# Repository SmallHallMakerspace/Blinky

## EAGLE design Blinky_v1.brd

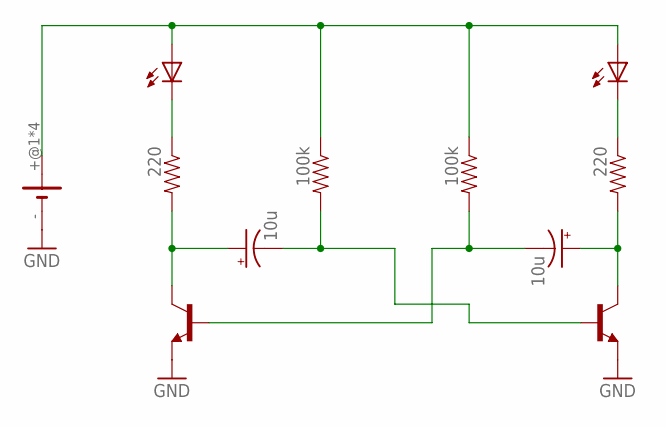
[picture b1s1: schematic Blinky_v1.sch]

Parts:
BT1: BAT-HLD-001-THM; LINX_BAT-HLD-001-THM
C1, C2: 10u; CPOL-RADIAL-10UF-25V
LED1, LED2: RED; LED5MM
R1, R2: 220; AXIAL-0.3
R3, R4: 100k; AXIAL-0.3
U$1, U$2: TRANSISTOR_NPN_2PTH; TO-92

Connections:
GND: BT1.-, U$1.3 (E), U$2.3 (E)
unnamed: LED2.K (C), R2.P$1 (1)
unnamed: C2.1 (+), R2.P$2 (2), U$2.1 (C)
unnamed: LED1.K (C), R1.P$1 (1)
unnamed: C1.1 (+), R1.P$2 (2), U$1.1 (C)
unnamed: BT1.+@1 (+), BT1.+@2 (+), BT1.+@3 (+), BT1.+@4 (+), LED1.A, LED2.A, R3.P$1 (1), R4.P$1 (1)
unnamed: C1.2 (-), R3.P$2 (2), U$2.2 (B)
unnamed: C2.2 (-), R4.P$2 (2), U$1.2 (B)

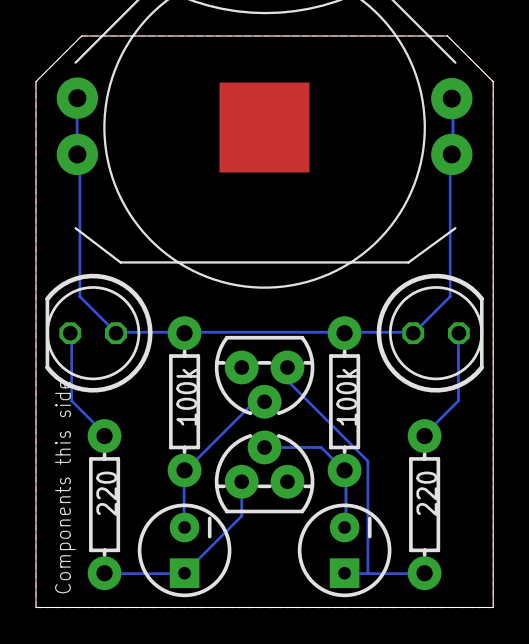
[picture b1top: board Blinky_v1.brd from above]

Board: 2 copper layers, 25.4 x 31.8 mm, 11 parts (0 on the bottom side), 8 nets.

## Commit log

2016-08-12 Initial import, very similar to what was ordered from OSH Park on August 11, 2016.
2016-08-12 Ignore files that eagle creates.
2016-08-12 Added good and bad soldering image, top and bottom text. All on bottom silkscreen.

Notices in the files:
Blinky_v1.brd:
Licensed CC-BY-SA
parts and their libraries:
SparkFun-Passives: Licensing: Creative Commons ShareAlike 4.0 International - https://creativecommons.org/licenses/by-sa/4.0
